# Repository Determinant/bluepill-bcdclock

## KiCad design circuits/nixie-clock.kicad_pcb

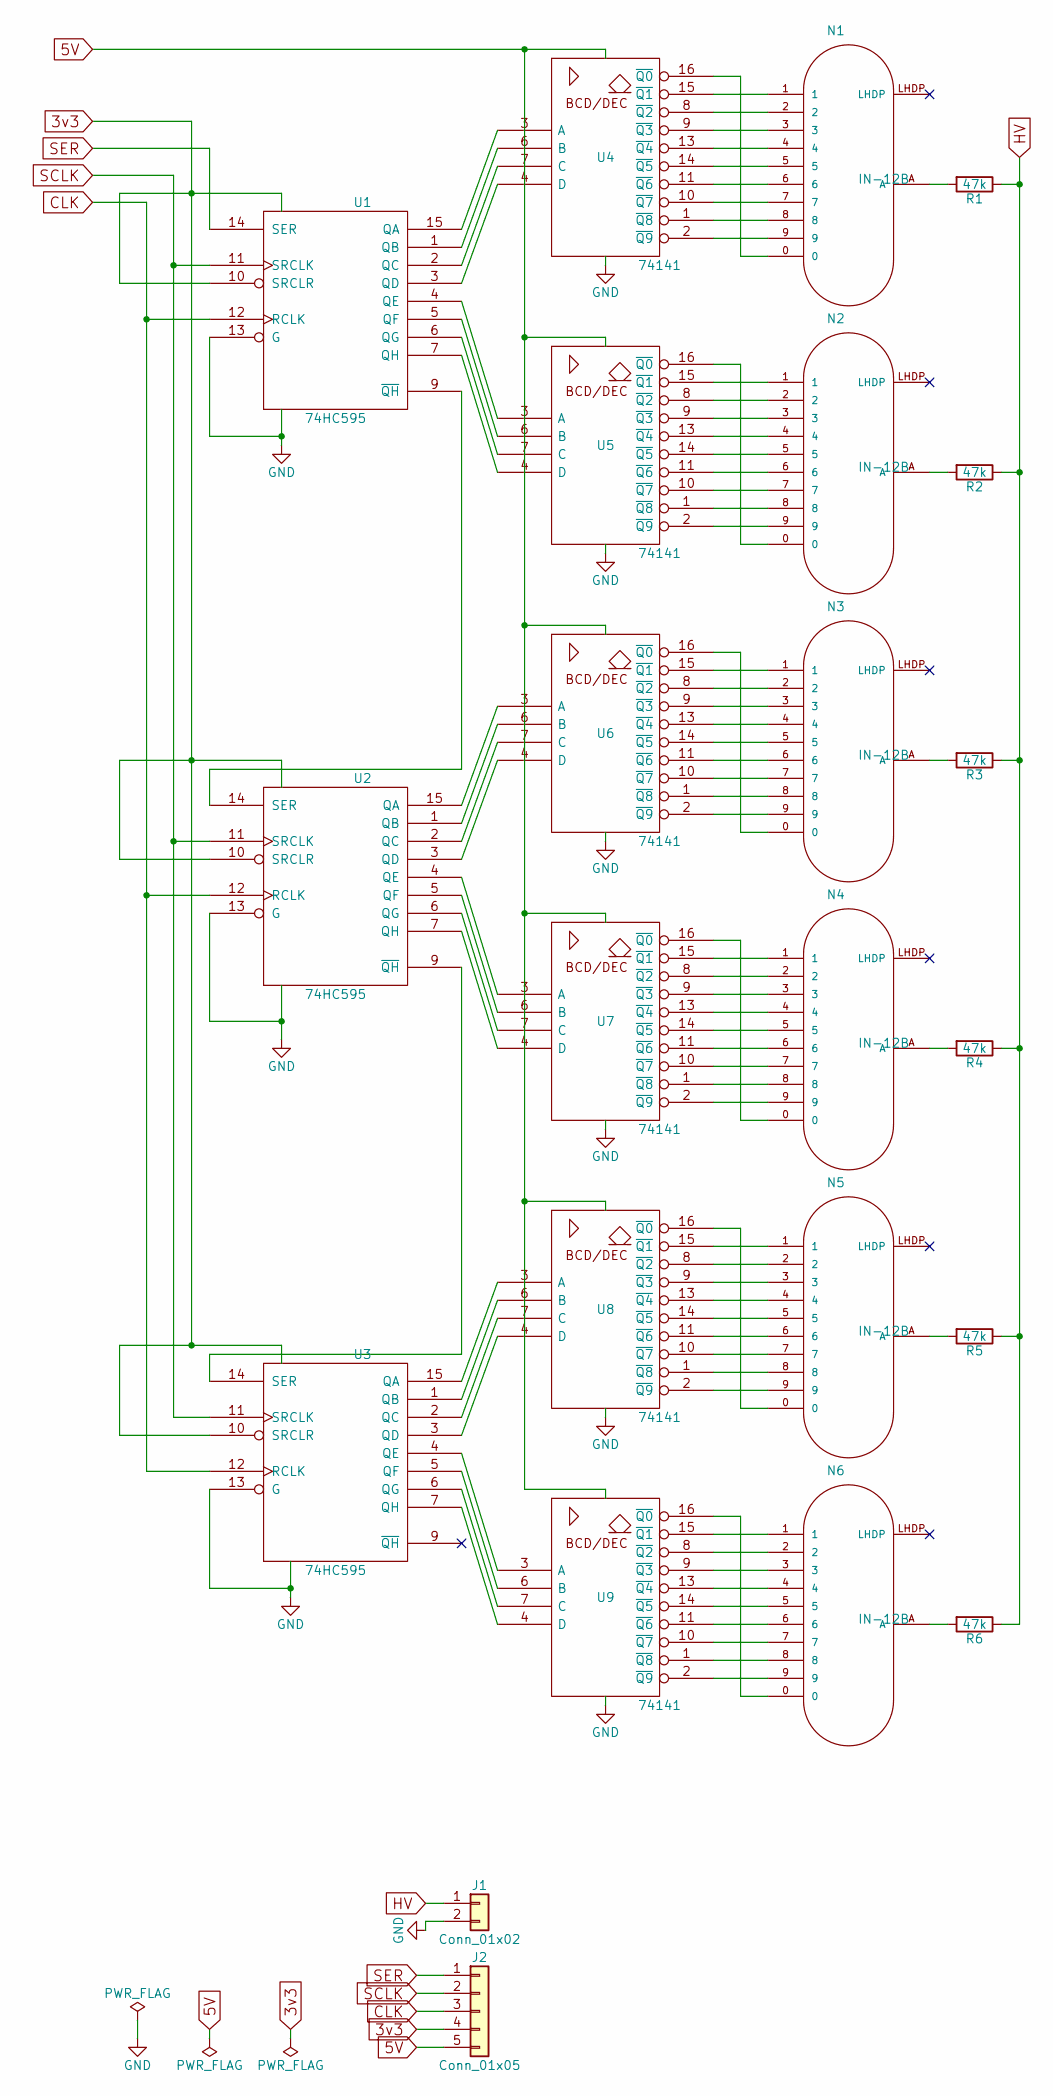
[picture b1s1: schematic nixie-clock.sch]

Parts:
J1: Conn_01x02; Pin_Header_Angled_1x02_Pitch2.00mm
J2: Conn_01x05; Pin_Header_Angled_1x05_Pitch2.00mm
N1, N2, N3, N4, N5, N6: IN-12B; russian-nixies-IN-12
R1, R2, R3, R4, R5, R6: 47k; R_Axial_DIN0204_L3.6mm_D1.6mm_P7.62mm_Horizontal
U1, U2, U3: 74HC595; DIP-16_W7.62mm
U4, U5, U6, U7, U8, U9: 74141; DIP-16_W7.62mm

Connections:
3v3: J2.4, U1.10 (SRCLR), U1.16 (VCC), U2.10 (SRCLR), U2.16 (VCC), U3.10 (SRCLR), U3.16 (VCC)
5V: J2.5, U4.5 (VDD), U5.5 (VDD), U6.5 (VDD), U7.5 (VDD), U8.5 (VDD), U9.5 (VDD)
CLK: J2.3, U1.12 (RCLK), U2.12 (RCLK), U3.12 (RCLK)
GND: J1.2, U1.8 (GND), U1.13 (G), U2.8 (GND), U2.13 (G), U3.8 (GND), U3.13 (G), U4.12 (GND), U5.12 (GND), U6.12 (GND), U7.12 (GND), U8.12 (GND), U9.12 (GND)
HV: J1.1, R1.1, R2.1, R3.1, R4.1, R5.1, R6.1
unnamed: N1.0, U4.16 (~Q0)
unnamed: N1.1, U4.15 (~Q1)
unnamed: N1.2, U4.8 (~Q2)
unnamed: N1.3, U4.9 (~Q3)
unnamed: N1.4, U4.13 (~Q4)
unnamed: N1.5, U4.14 (~Q5)
unnamed: N1.6, U4.11 (~Q6)
unnamed: N1.7, U4.10 (~Q7)
unnamed: N1.8, U4.1 (~Q8)
unnamed: N1.9, U4.2 (~Q9)
unnamed: N1.A, R1.2
unnamed: N2.0, U5.16 (~Q0)
unnamed: N2.1, U5.15 (~Q1)
unnamed: N2.2, U5.8 (~Q2)
unnamed: N2.3, U5.9 (~Q3)
unnamed: N2.4, U5.13 (~Q4)
unnamed: N2.5, U5.14 (~Q5)
unnamed: N2.6, U5.11 (~Q6)
unnamed: N2.7, U5.10 (~Q7)
unnamed: N2.8, U5.1 (~Q8)
unnamed: N2.9, U5.2 (~Q9)
unnamed: N2.A, R2.2
unnamed: N3.0, U6.16 (~Q0)
unnamed: N3.1, U6.15 (~Q1)
unnamed: N3.2, U6.8 (~Q2)
unnamed: N3.3, U6.9 (~Q3)
unnamed: N3.4, U6.13 (~Q4)
unnamed: N3.5, U6.14 (~Q5)
unnamed: N3.6, U6.11 (~Q6)
unnamed: N3.7, U6.10 (~Q7)
unnamed: N3.8, U6.1 (~Q8)
unnamed: N3.9, U6.2 (~Q9)
unnamed: N3.A, R3.2
unnamed: N4.0, U7.16 (~Q0)
unnamed: N4.1, U7.15 (~Q1)
unnamed: N4.2, U7.8 (~Q2)
unnamed: N4.3, U7.9 (~Q3)
unnamed: N4.4, U7.13 (~Q4)
unnamed: N4.5, U7.14 (~Q5)
unnamed: N4.6, U7.11 (~Q6)
unnamed: N4.7, U7.10 (~Q7)
unnamed: N4.8, U7.1 (~Q8)
unnamed: N4.9, U7.2 (~Q9)
unnamed: N4.A, R4.2
unnamed: N5.0, U8.16 (~Q0)
unnamed: N5.1, U8.15 (~Q1)
unnamed: N5.2, U8.8 (~Q2)
unnamed: N5.3, U8.9 (~Q3)
unnamed: N5.4, U8.13 (~Q4)
unnamed: N5.5, U8.14 (~Q5)
unnamed: N5.6, U8.11 (~Q6)
unnamed: N5.7, U8.10 (~Q7)
unnamed: N5.8, U8.1 (~Q8)
unnamed: N5.9, U8.2 (~Q9)
unnamed: N5.A, R5.2
unnamed: N6.0, U9.16 (~Q0)
unnamed: N6.1, U9.15 (~Q1)
unnamed: N6.2, U9.8 (~Q2)
unnamed: N6.3, U9.9 (~Q3)
unnamed: N6.4, U9.13 (~Q4)
unnamed: N6.5, U9.14 (~Q5)
unnamed: N6.6, U9.11 (~Q6)
unnamed: N6.7, U9.10 (~Q7)
unnamed: N6.8, U9.1 (~Q8)
unnamed: N6.9, U9.2 (~Q9)
unnamed: N6.A, R6.2
unnamed: U1.1 (QB), U4.6 (B)
unnamed: U1.2 (QC), U4.7 (C)
unnamed: U1.3 (QD), U4.4 (D)
unnamed: U1.4 (QE), U5.3 (A)
unnamed: U1.5 (QF), U5.6 (B)
unnamed: U1.6 (QG), U5.7 (C)
unnamed: U1.7 (QH), U5.4 (D)
unnamed: U1.9 (~QH), U2.14 (SER)
unnamed: U1.15 (QA), U4.3 (A)
unnamed: U2.1 (QB), U6.6 (B)
unnamed: U2.2 (QC), U6.7 (C)
unnamed: U2.3 (QD), U6.4 (D)
unnamed: U2.4 (QE), U7.3 (A)
unnamed: U2.5 (QF), U7.6 (B)
unnamed: U2.6 (QG), U7.7 (C)
unnamed: U2.7 (QH), U7.4 (D)
unnamed: U2.9 (~QH), U3.14 (SER)
unnamed: U2.15 (QA), U6.3 (A)
unnamed: U3.1 (QB), U8.6 (B)
unnamed: U3.2 (QC), U8.7 (C)
unnamed: U3.3 (QD), U8.4 (D)
unnamed: U3.4 (QE), U9.3 (A)
unnamed: U3.5 (QF), U9.6 (B)
unnamed: U3.6 (QG), U9.7 (C)
unnamed: U3.7 (QH), U9.4 (D)
unnamed: U3.15 (QA), U8.3 (A)
SCLK: J2.2, U1.11 (SRCLK), U2.11 (SRCLK), U3.11 (SRCLK)
SER: J2.1, U1.14 (SER)

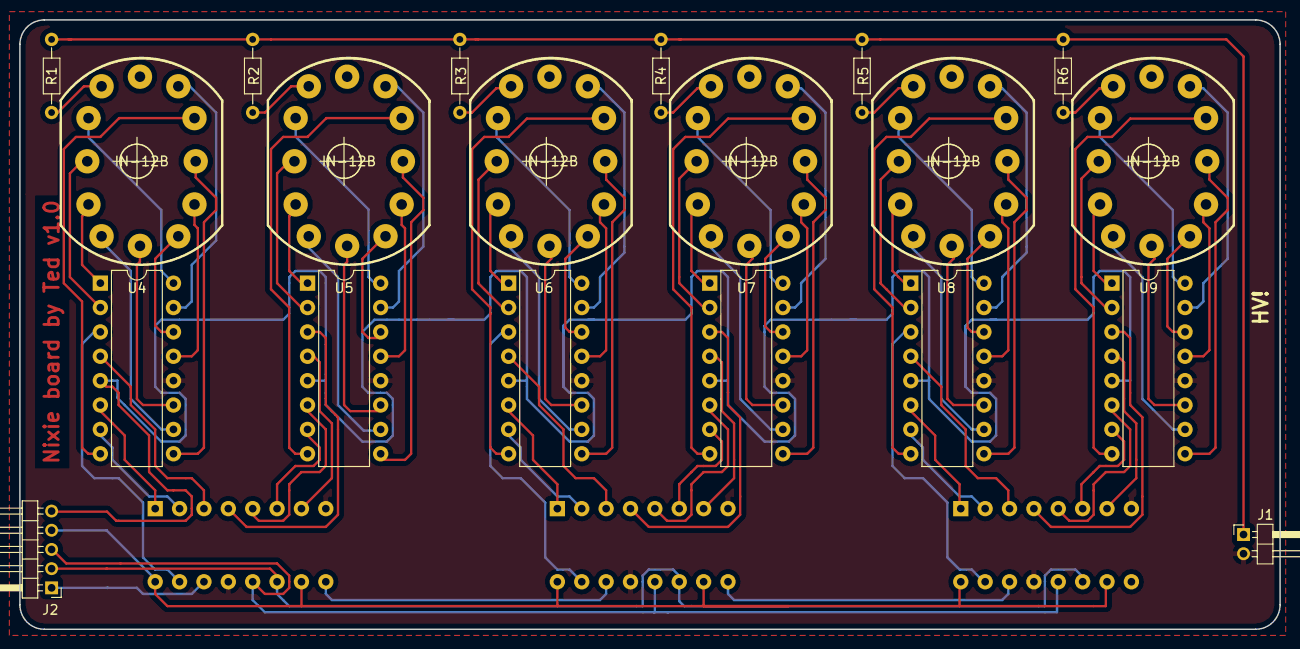
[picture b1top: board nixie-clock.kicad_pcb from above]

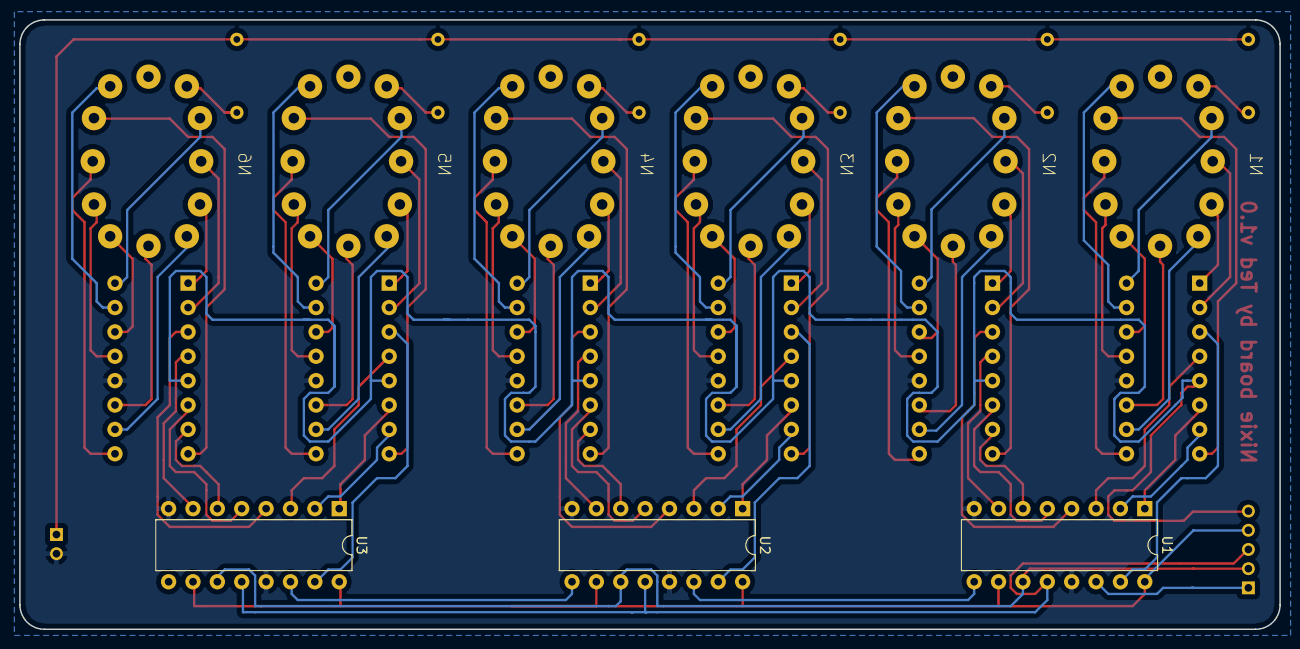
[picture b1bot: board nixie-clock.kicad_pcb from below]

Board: 2 copper layers, 131.3 x 63.5 mm, 23 parts (3 on the bottom side), 99 nets.

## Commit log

2017-09-21 init
2017-09-22 basic functionality now works
2017-09-22 sync with ds3231 every 10s
2017-09-22 fix a bug in sysclock calc
2017-09-22 clean up code
2017-09-23 code refactor
2017-09-28 add at24c support
2017-09-29 support arbitrary write for EEPROM
2017-10-18 code refactoring
2017-10-18 add mutex impl
2017-10-18 reduce unsafe blocks
2017-10-19 add timer impl
2017-10-23 add panels and time editing
2017-10-23 add temperature panel
2017-10-24 add countdown panel
2017-10-27 add button 2
2017-10-28 multiplex the event timer and fix bugs
2017-10-28 add the binary rom
2017-10-28 add schematic and pcb design
2017-10-30 support auto display on/off
2017-10-30 add the setting panel
2017-10-31 support continous press
2017-10-31 support immediate press
2017-11-01 refactor the code
2018-10-15 update the code for new build env
